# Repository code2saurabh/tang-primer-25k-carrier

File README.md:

# Tang Primer 25K carrier board (open hardware)

A 4-layer carrier board for the **Sipeed Tang Primer 25K** FPGA module (Gowin GW5A-LV25). It makes the bare
module usable when Sipeed's official 25K Dock is out of stock, which in India it has been for months.

It is **pin-compatible with Sipeed's 25K Dock**: the same 40-pin header, three PMOD ports, UART and user buttons
S1/S2. Sipeed's examples and existing Dock `.cst` constraint files work unchanged. The board is powered from
USB-C and programmed through a JTAG header that uses the Dock's J7 pinout.

> **Status: designed and checked, NOT yet built.** This is an untested first prototype.
> - DRC: 0 errors, 0 unconnected; schematic parity 0. The 93 remaining warnings are documented in `PLAN.md`.
> - On 25 Nov 2026 a polarity error on the TVS diode D1 was found in JLCPCB's 3D preview and fixed (PLAN.md
>   D21). `verify_schematic.py` now checks diode polarity.
> - If you build it, please open an issue with your results, good or bad.

The whole design was produced by scripts and AI-assisted engineering (Claude), with every step checked by
KiCad's own ERC/DRC and by independent rule scripts. [PLAN.md](PLAN.md) records every fact, source and decision
(D1–D21), including the mistakes.

## Folders
| Path | What |
|---|---|
| `PLAN.md` | Plan, status, verified facts, decisions D1–D21 |
| `pinout_v2.csv` | All 120 module pins, checked against several official sources |
| `kicad/carrier_v2.kicad_pro` / `.kicad_sch` | KiCad 10 project and schematic. **Generated; don't hand-edit** (see below) |
| `kicad/carrier_v2_schematic.pdf` | Schematic PDF for reading |
| `kicad/carrier_v2.kicad_pcb` | PCB: Dock outline and placement, fully routed, pours filled. **Generated**: `gen_pcb.py` → `route_pcb.py` → `cleanup_pcb.py` |
| `kicad/*.png` | 3D renders and the F.Cu / In2.Cu / B.Cu copper |
| `kicad/drc_report.txt` | Latest full DRC report |
| `fab/carrier_v2_jlcpcb_gerbers.zip` | Gerbers plus drill, ready to upload (JLCPCB format) |
| `fab/carrier_v2_jlcpcb_bom.csv`, `fab/carrier_v2_jlcpcb_cpl.csv` | JLCPCB assembly files (every line has an LCSC part number) |
| `fab/carrier_v2_bom_mpn.csv` | Vendor-neutral BOM: manufacturer, MPN, LCSC number and polarity notes, for any assembler |
| `fab/hand_solder.csv`, `fab/ORDERING.md` | Through-hole parts to solder yourself; step-by-step order settings and checks |
| `kicad/carrier_v2.pretty/` | Project footprint: Sipeed's official DF40 socket land pattern |
| `tools/` | Generators and checkers (see below) |
| `sources/SOURCES.md` | Index of the official Sipeed, Gowin and Hirose documents used, and where to get them |
| `reference_v1/` | The old v1 pin list, kept only for comparison |

## Ordering
Read [fab/ORDERING.md](fab/ORDERING.md) first. In short:
- 4 layers, 1.6 mm, **ENIG** finish (needed for the 0.4 mm-pitch DF40 sockets).
- 0.1/0.1 mm track/space, 0.2 mm vias.
- Top-side assembly.

JLCPCB builds it as designed. Some Indian fabs (for example PCB Power) have also confirmed the design rules are
feasible. Total for 5 boards with 2 assembled was about ₹10–13k (Nov 2026).

## Board summary
- **Module:** 2× Hirose DF40C-60DS-0.4V(51) receptacles (1.5 mm stack) on Sipeed's official land pattern.
- **Power:** USB-C (power only) → 2 A fuse → +5 V, protected by an SMF5.0A unidirectional TVS diode (cathode to
  VBUS). The module's own 3.3 V output feeds VCCIO0/1, 2/3 and 6/7 through ferrite beads.
  - Keep total 3.3 V draw from the headers under about 500 mA.
- **Headers:**
  - J3: 2×20, same as Dock J3 (38 GPIO, +5 V, GND).
  - J4–J6: PMOD, same as the Dock.
  - J7: JTAG.
  - J8: UART (GND, FPGA RX = B3, FPGA TX = C3).
  - J9: AUX (IOT23A/B).
- **Configuration and buttons:**
  - READY/DONE LEDs.
  - RECONFIG button.
  - S1/S2 user buttons on H11/H10, active high (enable the FPGA pull-down in your design).
- **Programming:** the board has **no onboard USB programmer**. Use an FT2232H or CH347 USB-JTAG adapter on J7
  with openFPGALoader, or a Gowin cable.
- **Not broken out:** the module's MIPI D-PHY lanes (the Dock doesn't use them either).

## Rebuild and re-check everything
Requirements:
- KiCad 10;
- Python 3 with `pymupdf`;
- Java 17+ and [Freerouting 1.9.0](https://github.com/freerouting/freerouting/releases/tag/v1.9.0), with the
  environment variable `FREEROUTING_JAR` pointing at the jar.

**Source documents:** the vendor PDFs and CAD files are copyrighted by Sipeed, Gowin and Hirose, so they are not
in this repo. Download them into `sources/` as listed in [sources/SOURCES.md](sources/SOURCES.md). Two small
derived files are included so the PCB step works without them: `sources/sipeed_official/dock_layout.json` and
`sources/ball_map_from_schematic.csv`. `make_df40_footprint.py` needs Sipeed's footprint file; the generated
footprint is already in `kicad/carrier_v2.pretty/`.

Run these from `tools/`. The paths assume KiCad's default Windows install, so adjust them on Linux or macOS.
```bash
python build_pinout.py
python make_df40_footprint.py
python gen_schematic.py
"C:\Program Files\KiCad\10.0\bin\kicad-cli.exe" sch upgrade ..\kicad\carrier_v2.kicad_sch
python verify_schematic.py
"C:\Program Files\KiCad\10.0\bin\python.exe" gen_pcb.py
"C:\Program Files\KiCad\10.0\bin\python.exe" route_pcb.py 60
"C:\Program Files\KiCad\10.0\bin\python.exe" cleanup_pcb.py
"C:\Program Files\KiCad\10.0\bin\kicad-cli.exe" pcb drc --severity-all --schematic-parity --refill-zones -o ..\kicad\drc_report.txt ..\kicad\carrier_v2.kicad_pcb
python make_fab.py
```
What the scripts do:
- `route_pcb.py` rebuilds the board with `gen_pcb.py`, exports it, routes it with Freerouting 1.9.0, imports the
  result and fills the pours.
- `cleanup_pcb.py` removes dangling copper and fixes too-close vias, driven only by KiCad's DRC, and undoes any
  change that breaks a connection.
- `make_fab.py` writes the Gerbers, drill, BOMs and CPL into `fab/`.
- `extract_dock_layout.py` re-creates `dock_layout.json` from the Dock iBOM (needs `pip install lzstring`).

`verify_schematic.py` exits non-zero on any problem. It checks:
- ERC reports 0 violations.
- The netlist matches the generator's intent.
- Module pins match the official pinout.
- All 68 GPIOs are broken out.
- Header signals match the Dock PDF, and differential pairs sit side by side.
- The pull-up/pull-down, power, JTAG and UART rules hold.
- Diode polarity is correct.
- Every symbol pin has a pad in its footprint.

To change the design, edit `tools/gen_schematic.py` and re-run the chain.

## Licence
- Hardware design files (schematic, PCB, footprints, fabrication outputs): **CERN-OHL-P-2.0** ([LICENSE](LICENSE)).
- Scripts in `tools/` and `reference_v1/`: **MIT** ([tools/LICENSE](tools/LICENSE)).

Tang Primer, Sipeed, Gowin and Hirose are trademarks of their owners. This project is not affiliated with them.

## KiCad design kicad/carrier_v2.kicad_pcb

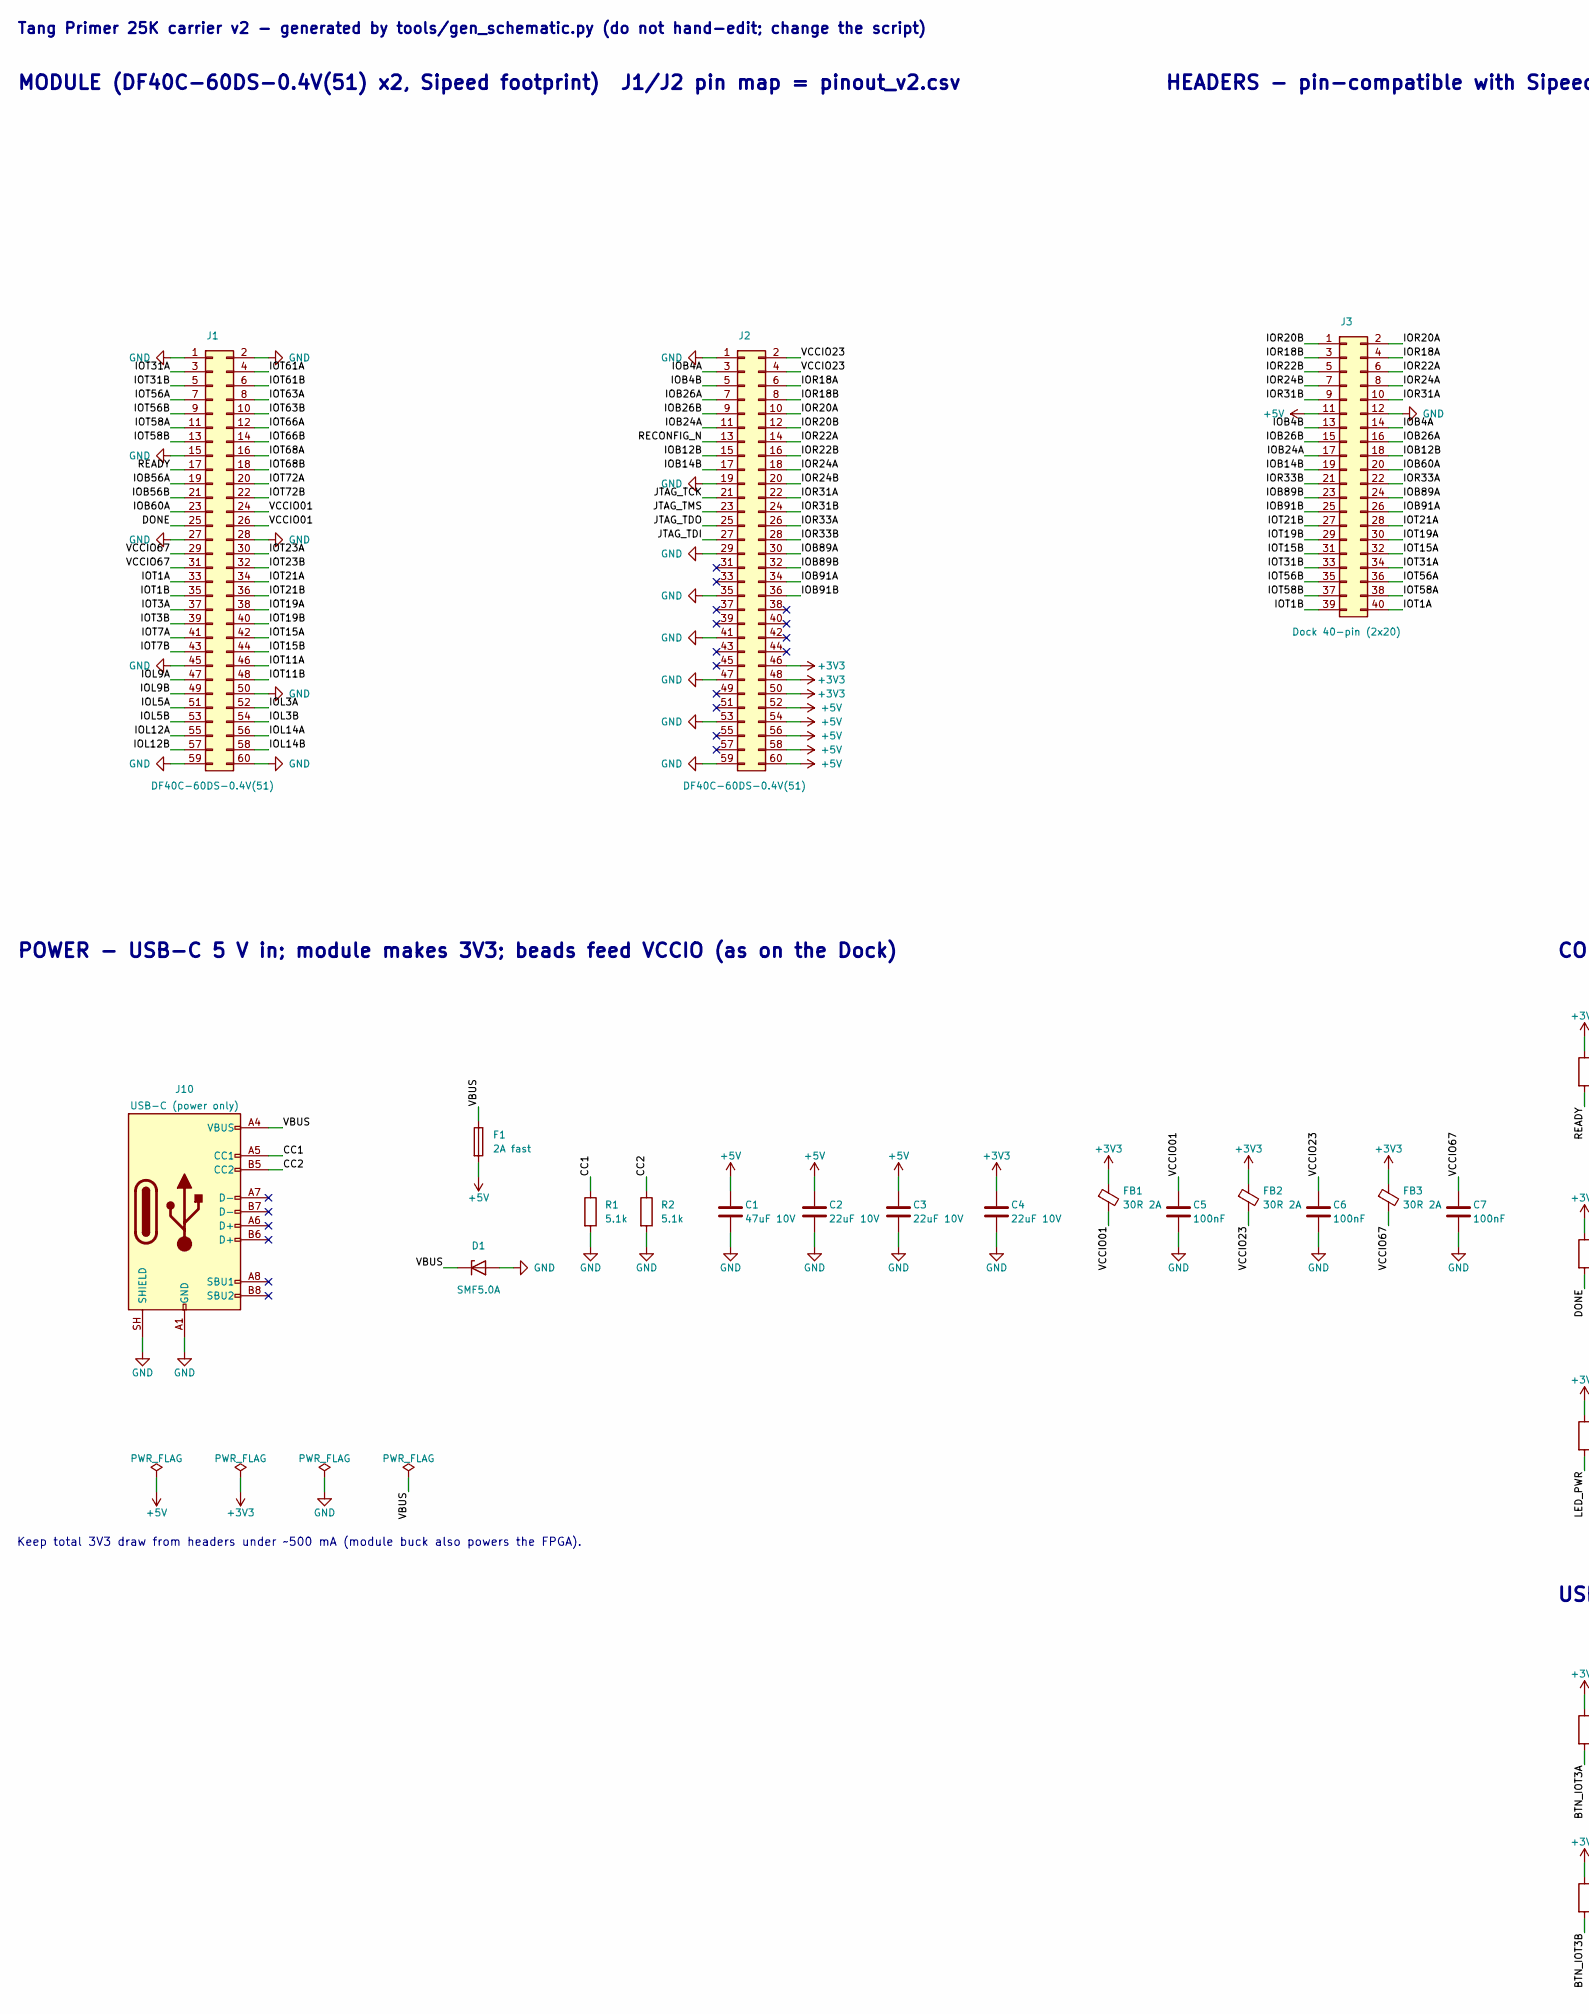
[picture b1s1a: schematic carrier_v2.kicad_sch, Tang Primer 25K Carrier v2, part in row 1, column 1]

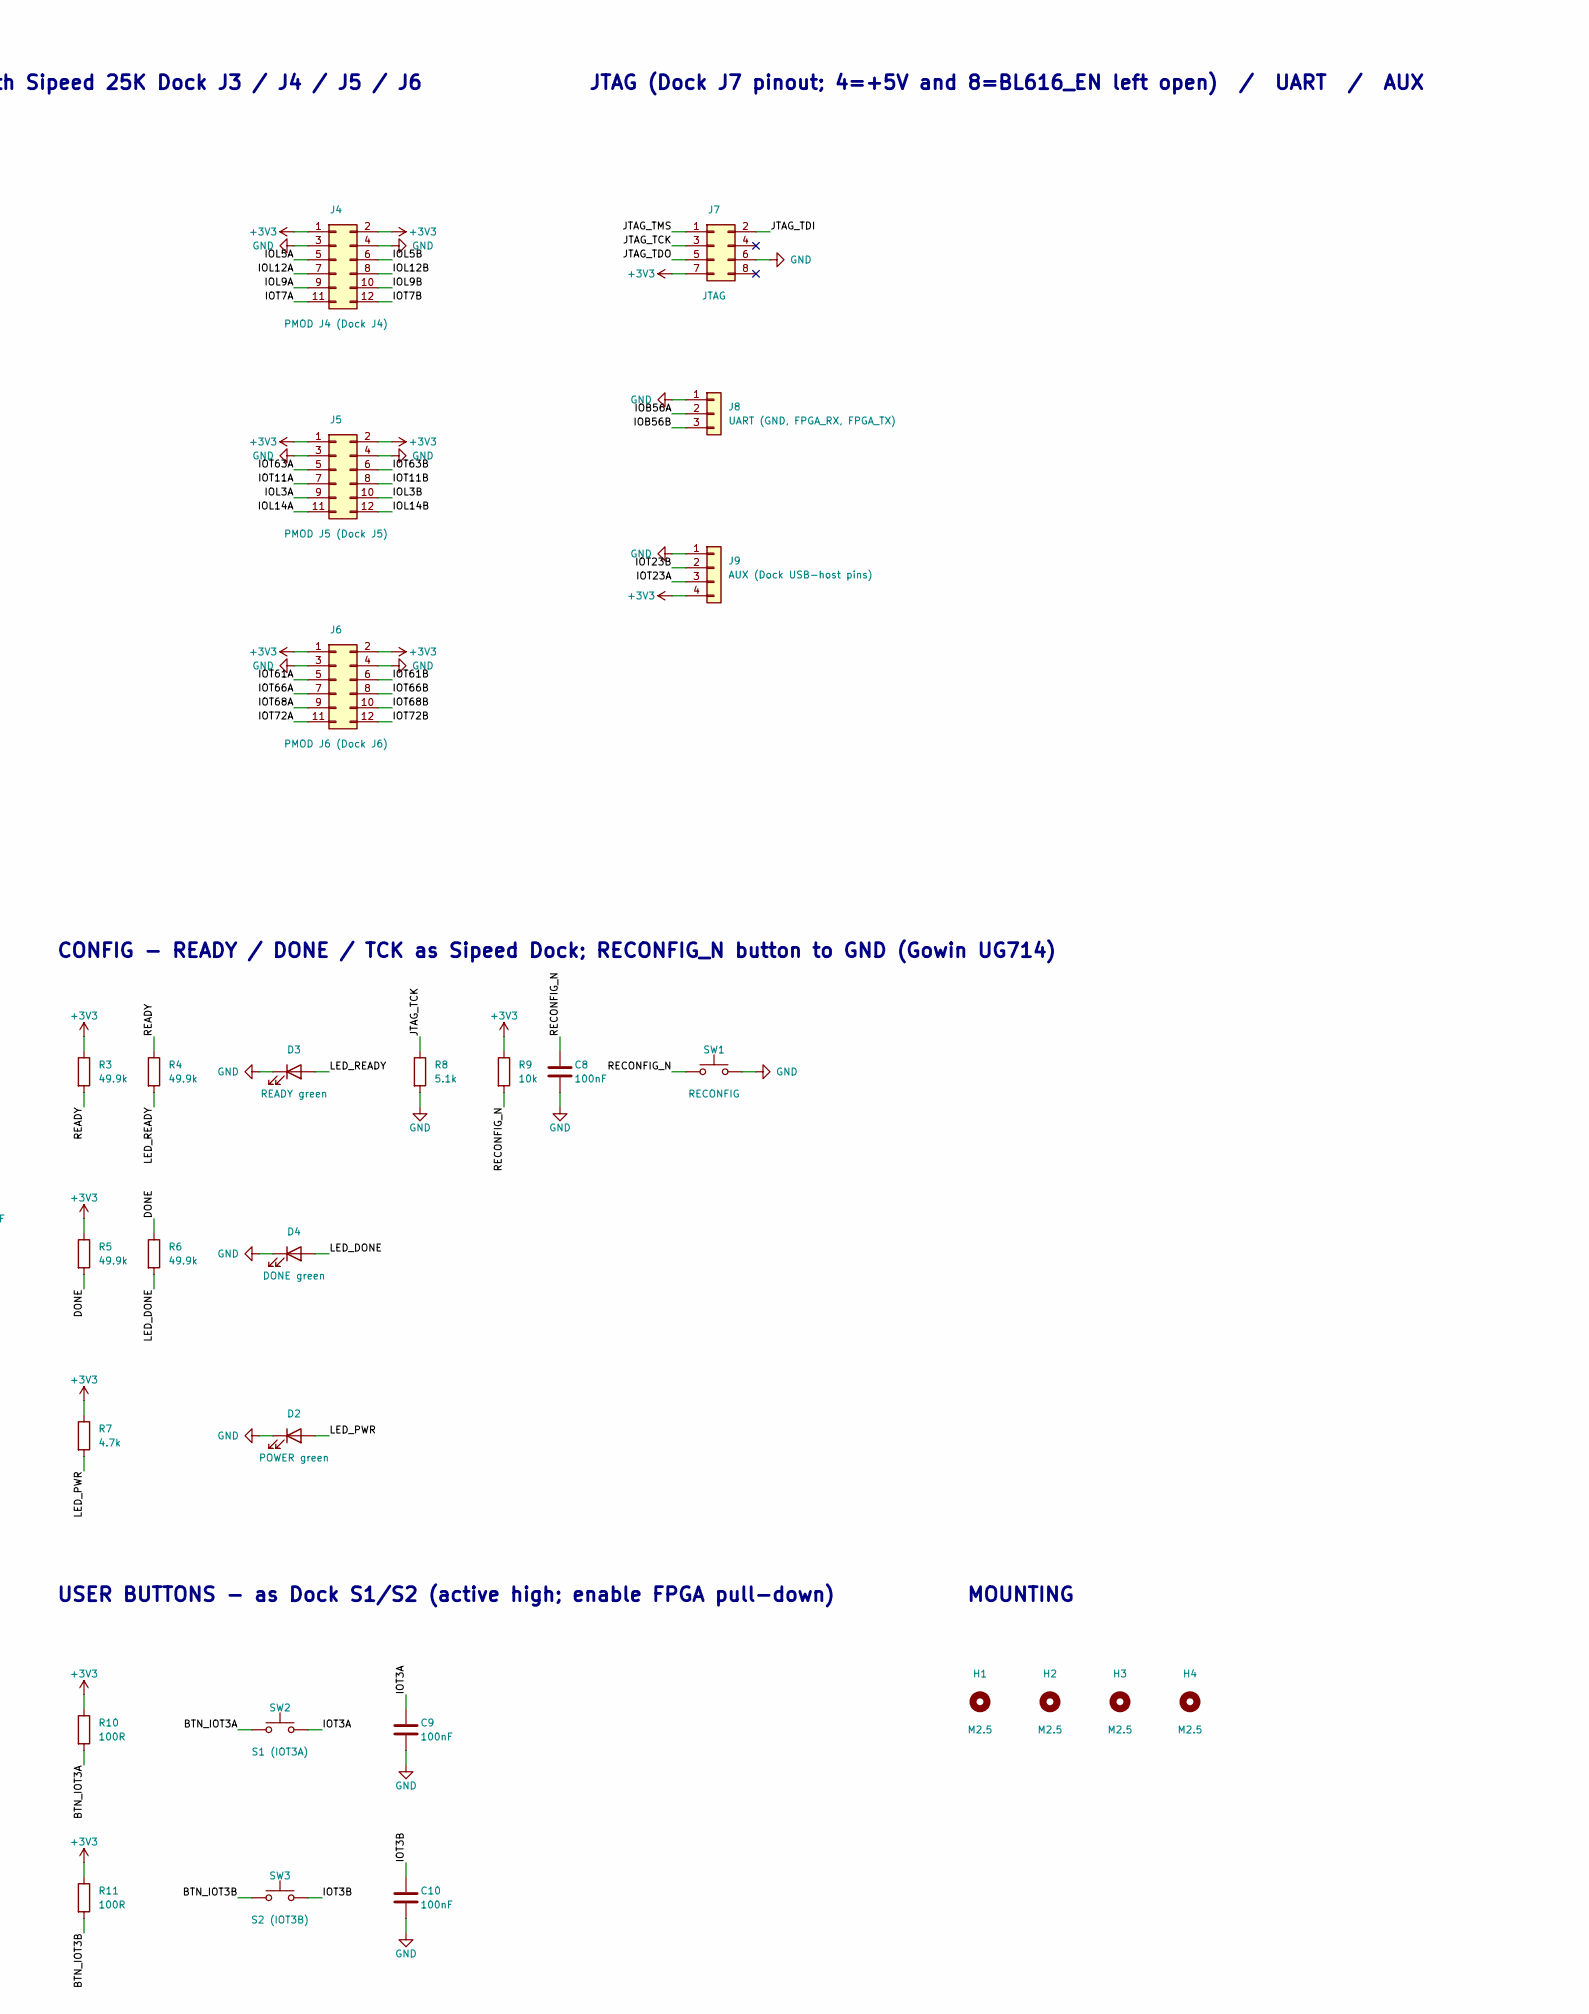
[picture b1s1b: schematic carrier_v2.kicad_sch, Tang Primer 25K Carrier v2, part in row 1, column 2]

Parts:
C1: 47uF 10V; C_1206_3216Metric
C2, C3, C4: 22uF 10V; C_0805_2012Metric
C5, C6, C7, C8, C9, C10: 100nF; C_0402_1005Metric
D1: SMF5.0A; D_SOD-123F; MPN SMF5.0A (5 V unidirectional TVS)
D2: POWER green; LED_0603_1608Metric
D3: READY green; LED_0603_1608Metric
D4: DONE green; LED_0603_1608Metric
F1: 2A fast; Fuse_1206_3216Metric; MPN 1206 2A fast-acting (e.g. Littelfuse 04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
FB1, FB2, FB3: 30R 2A; L_0603_1608Metric; MPN Sunlord GZ1608D300TF (30R@100MHz, 2A; D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
H1, H2, H3, H4: M2.5; MountingHole_2.7mm_M2.5
J1, J2: DF40C-60DS-0.4V(51); DF40C-60DS-0.4V_51_Sipeed; MPN Hirose DF40C-60DS-0.4V(51)
J3: Dock 40-pin (2x20); PinHeader_2x20_P2.54mm_Vertical
J4: PMOD J4 (Dock J4); PinSocket_2x06_P2.54mm_Horizontal
J5: PMOD J5 (Dock J5); PinSocket_2x06_P2.54mm_Horizontal
J6: PMOD J6 (Dock J6); PinSocket_2x06_P2.54mm_Horizontal
J7: JTAG; PinHeader_2x04_P2.54mm_Vertical
J8: UART (GND, FPGA_RX, FPGA_TX); PinHeader_1x03_P2.54mm_Vertical
J9: AUX (Dock USB-host pins); PinHeader_1x04_P2.54mm_Vertical
J10: USB-C (power only); USB_C_Receptacle_HRO_TYPE-C-31-M-12; MPN HRO TYPE-C-31-M-12
R1, R2, R8: 5.1k; R_0402_1005Metric
R3, R4, R5, R6: 49.9k; R_0402_1005Metric
R7: 4.7k; R_0402_1005Metric
R9: 10k; R_0402_1005Metric
R10, R11: 100R; R_0402_1005Metric
SW1: RECONFIG; SW_Push_1P1T_XKB_TS-1187A; MPN XKB TS-1187A-B-A-B
SW2: S1 (IOT3A); SW_Push_1P1T_XKB_TS-1187A; MPN XKB TS-1187A-B-A-B
SW3: S2 (IOT3B); SW_Push_1P1T_XKB_TS-1187A; MPN XKB TS-1187A-B-A-B

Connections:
+3V3: C4.1, FB1.1, FB2.1, FB3.1, J2.46, J2.48, J2.50, J4.1, J4.2, J5.1, J5.2, J6.1, J6.2, J7.7, J9.4, R3.1, R5.1, R7.1, R9.1, R10.1, R11.1
+5V: C1.1, C2.1, C3.1, F1.2, J2.52, J2.54, J2.56, J2.58, J2.60, J3.11
/BTN_IOT3A: R10.2, SW2.1
/BTN_IOT3B: R11.2, SW3.1
/CC1: J10.A5 (CC1), R1.1
/CC2: J10.B5 (CC2), R2.1
/DONE: J1.25, R5.2, R6.1
/IOB4A: J2.3, J3.14
/IOB4B: J2.5, J3.13
/IOB12B: J2.15, J3.18
/IOB14B: J2.17, J3.19
/IOB24A: J2.11, J3.17
/IOB26A: J2.7, J3.16
/IOB26B: J2.9, J3.15
/IOB56A: J1.19, J8.2
/IOB56B: J1.21, J8.3
/IOB60A: J1.23, J3.20
/IOB89A: J2.30, J3.24
/IOB89B: J2.32, J3.23
/IOB91A: J2.34, J3.26
/IOB91B: J2.36, J3.25
/IOL3A: J1.52, J5.9
/IOL3B: J1.54, J5.10
/IOL5A: J1.51, J4.5
/IOL5B: J1.53, J4.6
/IOL9A: J1.47, J4.9
/IOL9B: J1.49, J4.10
/IOL12A: J1.55, J4.7
/IOL12B: J1.57, J4.8
/IOL14A: J1.56, J5.11
/IOL14B: J1.58, J5.12
/IOR18A: J2.6, J3.4
/IOR18B: J2.8, J3.3
/IOR20A: J2.10, J3.2
/IOR20B: J2.12, J3.1
/IOR22A: J2.14, J3.6
/IOR22B: J2.16, J3.5
/IOR24A: J2.18, J3.8
/IOR24B: J2.20, J3.7
/IOR31A: J2.22, J3.10
/IOR31B: J2.24, J3.9
/IOR33A: J2.26, J3.22
/IOR33B: J2.28, J3.21
/IOT1A: J1.33, J3.40
/IOT1B: J1.35, J3.39
/IOT3A: C9.1, J1.37, SW2.2
/IOT3B: C10.1, J1.39, SW3.2
/IOT7A: J1.41, J4.11
/IOT7B: J1.43, J4.12
/IOT11A: J1.46, J5.7
/IOT11B: J1.48, J5.8
/IOT15A: J1.42, J3.32
/IOT15B: J1.44, J3.31
/IOT19A: J1.38, J3.30
/IOT19B: J1.40, J3.29
/IOT21A: J1.34, J3.28
/IOT21B: J1.36, J3.27
/IOT23A: J1.30, J9.3
/IOT23B: J1.32, J9.2
/IOT31A: J1.3, J3.34
/IOT31B: J1.5, J3.33
/IOT56A: J1.7, J3.36
/IOT56B: J1.9, J3.35
/IOT58A: J1.11, J3.38
/IOT58B: J1.13, J3.37
/IOT61A: J1.4, J6.5
/IOT61B: J1.6, J6.6
/IOT63A: J1.8, J5.5
/IOT63B: J1.10, J5.6
/IOT66A: J1.12, J6.7
/IOT66B: J1.14, J6.8
/IOT68A: J1.16, J6.9
/IOT68B: J1.18, J6.10
/IOT72A: J1.20, J6.11
/IOT72B: J1.22, J6.12
/JTAG_TCK: J2.21, J7.3, R8.1
/JTAG_TDI: J2.27, J7.2
/JTAG_TDO: J2.25, J7.5
/JTAG_TMS: J2.23, J7.1
/LED_DONE: D4.2 (A), R6.2
/LED_PWR: D2.2 (A), R7.2
/LED_READY: D3.2 (A), R4.2
/READY: J1.17, R3.2, R4.1
/RECONFIG_N: C8.1, J2.13, R9.2, SW1.1
/VBUS: D1.1 (K), F1.1, J10.A4 (VBUS), J10.A9 (VBUS), J10.B4 (VBUS), J10.B9 (VBUS)
/VCCIO01: C5.1, FB1.2, J1.24, J1.26
/VCCIO23: C6.1, FB2.2, J2.2, J2.4
/VCCIO67: C7.1, FB3.2, J1.29, J1.31
GND: C1.2, C2.2, C3.2, C4.2, C5.2, C6.2, C7.2, C8.2, C9.2, C10.2, D1.2 (A), D2.1 (K), D3.1 (K), D4.1 (K), J1.1, J1.2, J1.15, J1.27, J1.28, J1.45, J1.50, J1.59, J1.60, J2.1, J2.19, J2.29, J2.35, J2.41, J2.47, J2.53, J2.59, J3.12, J4.3, J4.4, J5.3, J5.4, J6.3, J6.4, J7.6, J8.1, J9.1, J10.A1 (GND), J10.A12 (GND), J10.B1 (GND), J10.B12 (GND), J10.SH (SHIELD), R1.2, R2.2, R8.2, SW1.2

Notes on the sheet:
CONFIG - READY / DONE / TCK as Sipeed Dock; RECONFIG_N button to GND (Gowin UG714)
Tang Primer 25K carrier v2 - generated by tools/gen_schematic.py (do not hand-edit; change the script)
POWER - USB-C 5 V in; module makes 3V3; beads feed VCCIO (as on the Dock)
Keep total 3V3 draw from headers under ~500 mA (module buck also powers the FPGA).
USER BUTTONS - as Dock S1/S2 (active high; enable FPGA pull-down)
MODULE (DF40C-60DS-0.4V(51) x2, Sipeed footprint) J1/J2 pin map = pinout_v2.csv
MOUNTING
HEADERS - pin-compatible with Sipeed 25K Dock J3 / J4 / J5 / J6
JTAG (Dock J7 pinout; 4=+5V and 8=BL616_EN left open) / UART / AUX

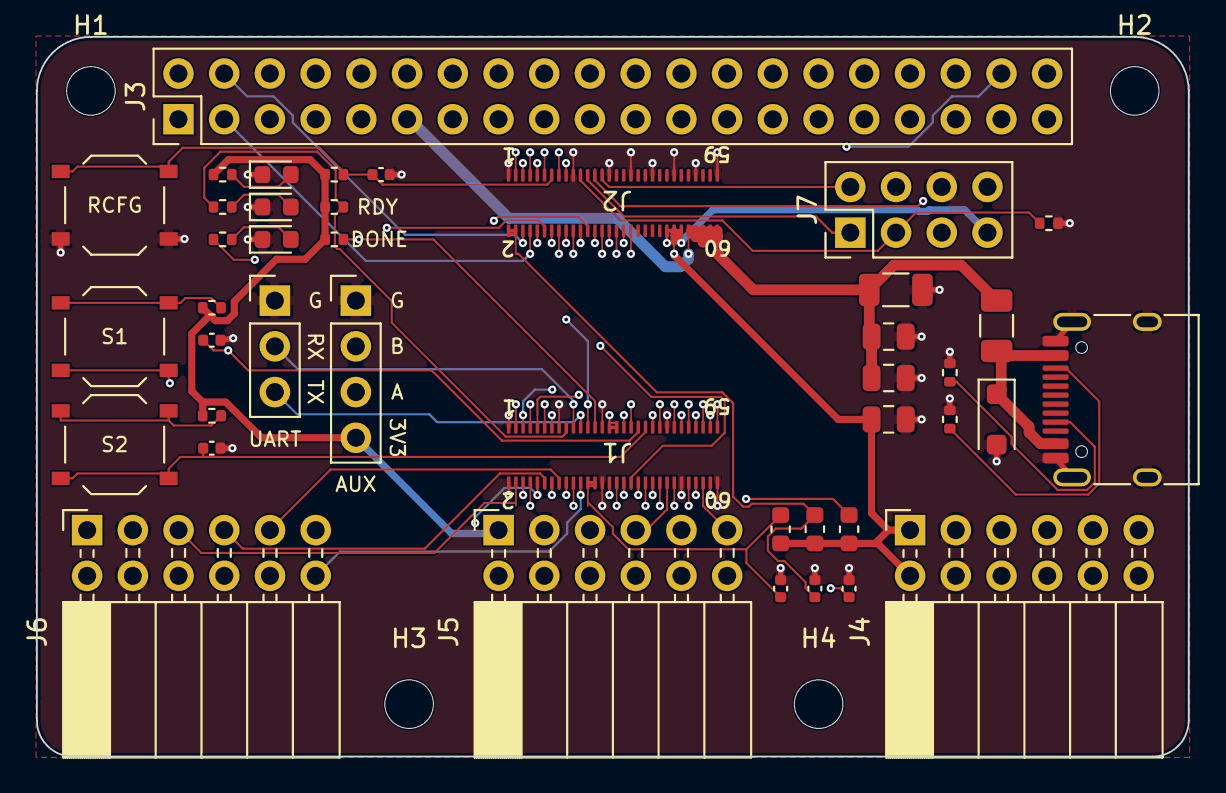
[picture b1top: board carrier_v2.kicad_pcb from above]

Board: 4 copper layers, 64.0 x 40.0 mm, 46 parts (0 on the bottom side), 89 nets.

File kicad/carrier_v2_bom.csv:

"Refs","Value","Footprint","Qty","DNP"
"C1","47uF 10V","Capacitor_SMD:C_1206_3216Metric","1",""
"C2","22uF 10V","Capacitor_SMD:C_0805_2012Metric","1",""
"C3","22uF 10V","Capacitor_SMD:C_0805_2012Metric","1",""
"C4","22uF 10V","Capacitor_SMD:C_0805_2012Metric","1",""
"C5","100nF","Capacitor_SMD:C_0402_1005Metric","1",""
"C6","100nF","Capacitor_SMD:C_0402_1005Metric","1",""
"C7","100nF","Capacitor_SMD:C_0402_1005Metric","1",""
"C8","100nF","Capacitor_SMD:C_0402_1005Metric","1",""
"C9","100nF","Capacitor_SMD:C_0402_1005Metric","1",""
"C10","100nF","Capacitor_SMD:C_0402_1005Metric","1",""
"D1","SMF5.0A","Diode_SMD:D_SOD-123F","1",""
"D2","POWER green","LED_SMD:LED_0603_1608Metric","1",""
"D3","READY green","LED_SMD:LED_0603_1608Metric","1",""
"D4","DONE green","LED_SMD:LED_0603_1608Metric","1",""
"F1","2A fast","Fuse:Fuse_1206_3216Metric","1",""
"FB1","30R 2A","Inductor_SMD:L_0603_1608Metric","1",""
"FB2","30R 2A","Inductor_SMD:L_0603_1608Metric","1",""
"FB3","30R 2A","Inductor_SMD:L_0603_1608Metric","1",""
"J1","DF40C-60DS-0.4V(51)","carrier_v2:DF40C-60DS-0.4V_51_Sipeed","1",""
"J2","DF40C-60DS-0.4V(51)","carrier_v2:DF40C-60DS-0.4V_51_Sipeed","1",""
"J3","Dock 40-pin (2x20)","Connector_PinHeader_2.54mm:PinHeader_2x20_P2.54mm_Vertical","1",""
"J4","PMOD J4 (Dock J4)","Connector_PinSocket_2.54mm:PinSocket_2x06_P2.54mm_Horizontal","1",""
"J5","PMOD J5 (Dock J5)","Connector_PinSocket_2.54mm:PinSocket_2x06_P2.54mm_Horizontal","1",""
"J6","PMOD J6 (Dock J6)","Connector_PinSocket_2.54mm:PinSocket_2x06_P2.54mm_Horizontal","1",""
"J7","JTAG","Connector_PinHeader_2.54mm:PinHeader_2x04_P2.54mm_Vertical","1",""
"J8","UART (GND, FPGA_RX, FPGA_TX)","Connector_PinHeader_2.54mm:PinHeader_1x03_P2.54mm_Vertical","1",""
"J9","AUX (Dock USB-host pins)","Connector_PinHeader_2.54mm:PinHeader_1x04_P2.54mm_Vertical","1",""
"J10","USB-C (power only)","Connector_USB:USB_C_Receptacle_HRO_TYPE-C-31-M-12","1",""
"R1","5.1k","Resistor_SMD:R_0402_1005Metric","1",""
"R2","5.1k","Resistor_SMD:R_0402_1005Metric","1",""
"R3","49.9k","Resistor_SMD:R_0402_1005Metric","1",""
"R4","49.9k","Resistor_SMD:R_0402_1005Metric","1",""
"R5","49.9k","Resistor_SMD:R_0402_1005Metric","1",""
"R6","49.9k","Resistor_SMD:R_0402_1005Metric","1",""
"R7","4.7k","Resistor_SMD:R_0402_1005Metric","1",""
"R8","5.1k","Resistor_SMD:R_0402_1005Metric","1",""
"R9","10k","Resistor_SMD:R_0402_1005Metric","1",""
"R10","100R","Resistor_SMD:R_0402_1005Metric","1",""
"R11","100R","Resistor_SMD:R_0402_1005Metric","1",""
"SW1","RECONFIG","Button_Switch_SMD:SW_Push_1P1T_XKB_TS-1187A","1",""
"SW2","S1 (IOT3A)","Button_Switch_SMD:SW_Push_1P1T_XKB_TS-1187A","1",""
"SW3","S2 (IOT3B)","Button_Switch_SMD:SW_Push_1P1T_XKB_TS-1187A","1",""

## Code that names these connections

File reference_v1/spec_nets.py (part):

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J2 = {
    1: (GND, "GND"),
    2: (P3V3, "P3V3"),          # VCCIO2/3
    3: ("IOB4A", "GPIO"),
    4: (P3V3, "P3V3"),          # VCCIO2/3
    5: ("IOB4B", "GPIO"),
    6: ("IOR18A", "GPIO"),
    7: ("IOB26A", "GPIO"),
    8: ("IOR18B", "GPIO"),
    9: ("IOB26B", "GPIO"),
    10: ("IOR20A", "GPIO"),
    11: ("IOB24A", "GPIO"),
    12: ("IOR20B", "GPIO"),
    13: ("RECONFIG", "CFG"),
    14: ("IOR22A", "GPIO"),
    15: ("IOB12B", "GPIO"),
    16: ("IOR22B", "GPIO"),
    17: ("IOB14B", "GPIO"),
    18: ("IOR24A", "GPIO"),
    19: (GND, "GND"),
    20: ("IOR24B", "GPIO"),
    21: ("JTAG_TCK", "JTAG"),
    22: ("IOR31A", "GPIO"),
    23: ("JTAG_TMS", "JTAG"),
    24: ("IOR31B", "GPIO"),
    25: ("JTAG_TDO", "JTAG"),
    26: ("IOR33A", "GPIO"),
    27: ("JTAG_TDI", "JTAG"),
    28: ("IOR33B", "GPIO"),
    29: (GND, "GND"),
    30: ("IOB89A", "GPIO"),
    31: ("M0_D3P", "MIPI"),
    32: ("IOB89B", "GPIO"),
    33: ("M0_D3N", "MIPI"),
    34: ("IOB91A", "GPIO"),
    35: (GND, "GND"),
    36: ("IOB91B", "GPIO"),
    37: ("M0_D2P", "MIPI"),
    38: ("VDD_1V8", "NC_PWR"),   # core board output, unused on carrier
    39: ("M0_D2N", "MIPI"),
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J1 = {
    1: (GND, "GND"),
    2: (GND, "GND"),
    3: ("IOT31A", "GPIO"),
    4: ("IOT61A", "GPIO"),
    5: ("IOT31B", "GPIO"),
    6: ("IOT61B", "GPIO"),
    7: ("UART_TX", "UART"),      # IOT56A on core board
    8: ("IOT63A", "GPIO"),
    9: ("UART_RX", "UART"),      # IOT56B
    10: ("IOT63B", "GPIO"),
    11: ("IOT58A", "GPIO"),
    12: ("IOT66A", "GPIO"),
    13: (GND, "GND"),
    14: ("IOT66B", "GPIO"),
    15: ("IOT58B", "GPIO"),
    16: ("IOT68A", "GPIO"),
    17: ("READY", "CFG"),
    18: ("IOT68B", "GPIO"),
    19: ("IOB56A", "GPIO"),
    20: ("IOT72A", "GPIO"),
    21: ("IOB56B", "GPIO"),
    22: ("IOT72B", "GPIO"),
    23: ("IOB60A", "GPIO"),
    24: (P3V3, "P3V3"),          # VCCIO0/1
    25: ("DONE", "CFG"),
    26: (P3V3, "P3V3"),          # VCCIO0/1
    27: (GND, "GND"),
    28: (GND, "GND"),
    29: (P3V3, "P3V3"),          # VCCIO6/7
    30: ("IOT23A", "GPIO"),
    31: (P3V3, "P3V3"),          # VCCIO6/7
    32: ("IOT23B", "GPIO"),
    33: ("IOT1A", "GPIO"),
    34: ("IOT21A", "GPIO"),
    35: ("IOT1B", "GPIO"),
    36: ("IOT21B", "GPIO"),
    37: ("IOT3A", "GPIO"),
    38: ("IOT19A", "GPIO"),
    39: ("IOT3B", "GPIO"),
    40: ("IOT19B", "GPIO"),
    41: ("IOT7A", "GPIO"),
    42: ("IOT15A", "GPIO"),
    43: ("IOT7B", "GPIO"),
    44: ("IOT15B", "GPIO"),
    45: (GND, "GND"),
    46: ("IOT11A", "GPIO"),
    47: ("IOL9A", "GPIO"),
    48: ("IOT11B", "GPIO"),
    49: ("IOL9B", "GPIO"),
    50: (GND, "GND"),
    51: ("IOL5A", "GPIO"),
    52: ("IOL3A", "GPIO"),
    53: ("IOL5B", "GPIO"),
    54: ("IOL3B", "GPIO"),
    55: ("IOL12A", "GPIO"),
    56: ("IOL14A", "GPIO"),
    57: ("IOL12B", "GPIO"),
    58: ("IOL14B", "GPIO"),
    59: (GND, "GND"),
    60: (GND, "GND"),
}
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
